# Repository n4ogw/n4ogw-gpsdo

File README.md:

# N4OGW GPS Disciplined oscillator

This GPSDO is based on the Lars Walenius design posted on eevblog.com:

[https://www.eevblog.com/forum/projects/lars-diy-gpsdo-with-arduino-and-1ns-resolution-tic/](https://www.eevblog.com/forum/projects/lars-diy-gpsdo-with-arduino-and-1ns-resolution-tic/)

The code has been translated from the Arduino to PIC, a
PIC18F27Q84. Unlike the original design external ICs are not used to
divide the 10 MHz input or measure the phase difference between the 1
PPS signal and the input. Instead, PIC Configurable Logic Cell (CLC)
units are used to perform these functions. The only active devices
besides the PIC are an op amp to buffer the PWM output controlling the
OCXO, and an op amp buffer and inverter gate to buffer the sine wave
OCXO output.

## Features

* Time interval Counter (TIC) with range of 1000 ns and 0.24 ns/bit
resolution (12 bit ADC)
* 16 bit PWM output for controlling the OCXO
* Direct frequency count of 10 MHz input to monitor frequency
* serial connections for computer and GPS
* LCD display showing UTC time, 6 character grid square, PWM value, lock status, number of satellites, and frequency counter error

---

## Description of hardware

The OCXO is a UCT 108663 with sine wave output. This OCXO requires a
12 V supply. The voltage on the EFC pin for mine is about 5 V when
tuned for 10 MHZ. RV2 is adjusted to first set the frequency of the
OCXO close to 10 MHz. The OCXO is buffered with an ADA4851 op amp and
sent to a 74LVC1G14 inverter before going to the PIC input. The PIC is
a PIC18F27Q84. A PIC18F26Q84 should also work.

 The PIC PWM output is buffered by two op amp stages using an
LM358. The PIC PWM output is set up as a single 16 bit PWM, but a
second pin is available for combining two PWM outputs.  A voltage
regulator on the board generates 5 V for the PIC and the GPS module.
Resistor R17 is not used. The value of R12/R13 depend on whether
current limiting is needed for the LCD backlight; mine did not need
it, so I used a zero ohm jumper. R23 is also a zero ohm jumper.

---

## Description of PIC code

MPLab 6.05; XC8 2.40

### Pins

RA0 - RA7 : (outputs) data for 2x16 LCD in 8 bit mode

RB0 : LCD RS (output)

RB1 : ADC input; reads TIC voltage

RB2 : (input) 10 MHz in

RB3 : (output) TIC to 3.9 k resistor

RB4 : button 1 (input)

RB5 : button 2 (input)

RB6 : ICSP clock

RB7 : ICSP data

RC0 : (input) PPS in

RC1 : LCD E (output)

RC2 : (input) UART2 RX (GPS)

RC3 : (output) UART2 TX (GPS)

RC4 : unused; can be used as second PWM output combined with RC5

RC5 : (output) 16 bit PWM output

RC6 : (output) UART1 TX (computer)

RC7 : (input) UART1 RX  (computer)

### Frequency counter

The PIC Signal Measurement Timer (SMT) is used as a frequency counter
to directly count the 10 MHz input signal. The SMT is used in Counter
mode; the signal comes from SMT1SIGPPS connected to RB2 (10 MHz); the
window comes from SMT1WINPPS connected to RC0 (PPS). Period is set to
0xFFFFFF, pulse width acquisition interrupt is enabled.

In this mode, the interrupt function `SMT1_PW_ACQ_ISR` is called at
every PPS pulse. This function updates the total count and the error
compared to 10 MHz.

### TIC

In the original design, an external IC is used to divide the 10 MHz
down to 1 MHz to drive the TIC. This function is instead done using
PIC CLC gates, one D-type flip-flop (CLC2) configured as divide-by-two
followed by three JK flip-flops (CLC3, CLC5, CLC6) configured as
divide-by-five.  CLCIN2 is connected to RB2, 10 MHz in. The output of
CLC6 is the 1.0 MHz signal.

####CLC2 (divide by 2)

####CLC3, CLC5, CLC6 (divide by 5)

####CLC3

####CLC5

####CLC6

####CLC1 and CLC7 (2 input D flip-flops with R)

Configured as the phase detector of the TIC. The inputs to CLC1 are
from CLC6 (1.0 MHz) and CLCIN3, which is mapped to RC0 (PPS). The
inputs to CLC7 are also PPS, and the output of CLC1. The output of
CLC7 drives the diode of the TIC circuit (RB3).

CLC1

CLC7

The reference voltage of the ADC is set to 1.024 V using the FVR
voltage reference. The ADC is set to trigger on the output of
CLC7. The ADC interrupt is enabled; `adcInterrupt()` is the interrupt
function which reads the value of the TIC. With a 12-bit ADC this is
in the range 0-4095.

### Buttons

The two input buttons are debounced using CLC8 and timer 6. CLCIN6 and
CLCIN7 are mapped to the two button pins, RB4 and RB5. Timer 6
is set up in monostable mode with a period of 15 ms, with the output
of CLC8 as the reset source. The timer interrupt function is
`buttonInterrupt()`, which checks to see which button was pressed.

####CLC8

####2x16 LCD

2x16 LCD library adopted from

[https://github.com/eziya/PIC18F_HD44780](https://github.com/eziya/PIC18F_HD44780)

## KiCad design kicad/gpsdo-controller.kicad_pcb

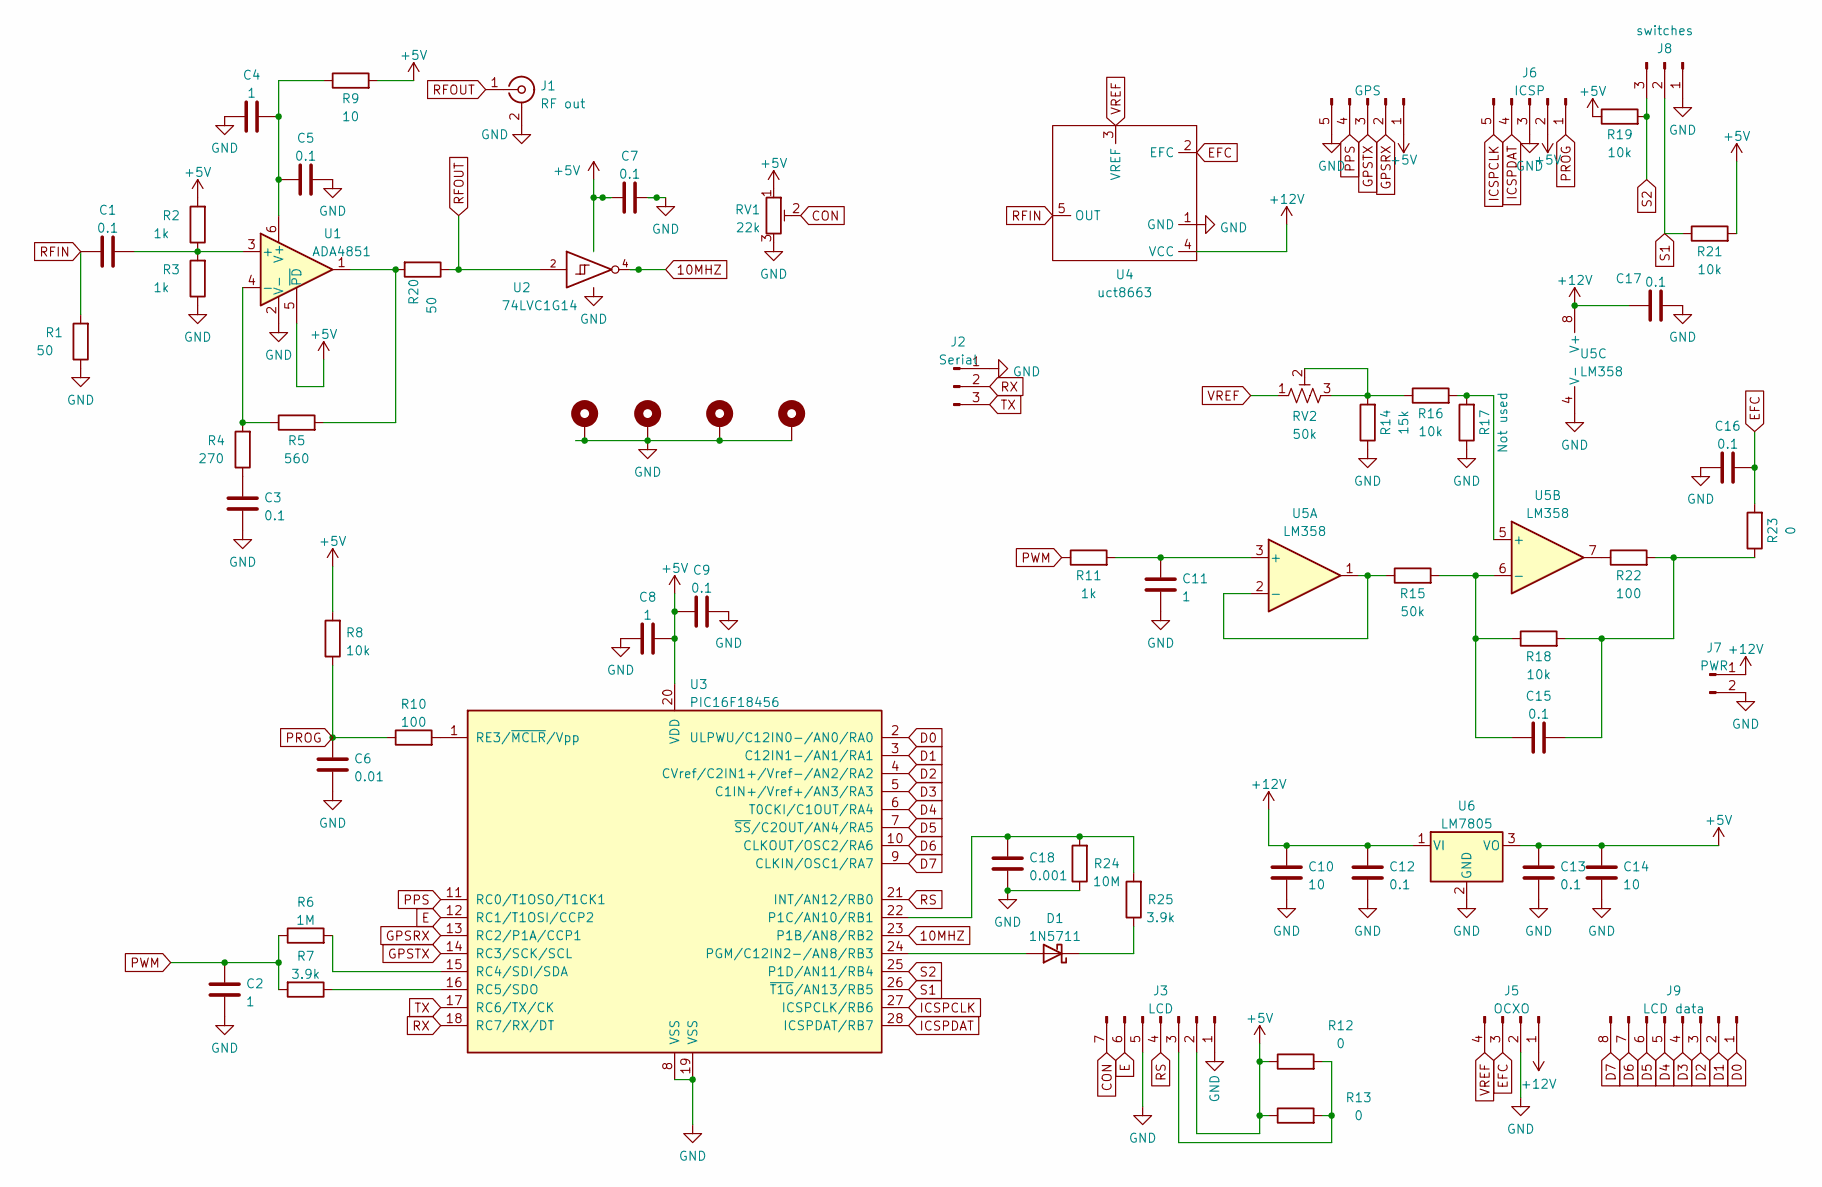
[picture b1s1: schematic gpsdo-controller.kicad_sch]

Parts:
C1, C3, C5, C7, C9, C12, C13, C15, C16, C17: 0.1; C_0805_2012Metric_Pad1.18x1.45mm_HandSolder
C2, C4, C8, C11: 1; C_0805_2012Metric_Pad1.18x1.45mm_HandSolder
C6: 0.01; C_0805_2012Metric_Pad1.18x1.45mm_HandSolder
C10, C14: 10; C_0805_2012Metric_Pad1.18x1.45mm_HandSolder
C18: 0.001; C_0805_2012Metric_Pad1.18x1.45mm_HandSolder
D1: 1N5711; D_SOD-123
H1, H2, H3, H4: GND; MountingHole_3.2mm_M3_DIN965_Pad
J1: RF out; SMA_Amphenol_901-144_Vertical
J2: Serial; PinHeader_1x03_P2.54mm_Vertical
J3: LCD; PinHeader_1x07_P2.54mm_Vertical
J4: GPS; PinHeader_1x05_P2.54mm_Vertical
J5: OCXO; PinHeader_1x04_P2.54mm_Vertical
J6: ICSP; PinHeader_1x05_P2.54mm_Vertical
J7: PWR; PinHeader_1x02_P2.54mm_Vertical
J8: switches; PinHeader_1x03_P2.54mm_Vertical
J9: LCD data; PinHeader_1x08_P2.54mm_Vertical
R1, R20: 50; R_0805_2012Metric_Pad1.20x1.40mm_HandSolder
R2, R3, R11: 1k; R_0805_2012Metric_Pad1.20x1.40mm_HandSolder
R4: 270; R_0805_2012Metric_Pad1.20x1.40mm_HandSolder
R5: 560; R_0805_2012Metric_Pad1.20x1.40mm_HandSolder
R6: 1M; R_0805_2012Metric_Pad1.20x1.40mm_HandSolder
R7, R25: 3.9k; R_0805_2012Metric_Pad1.20x1.40mm_HandSolder
R8, R16, R18, R19, R21: 10k; R_0805_2012Metric_Pad1.20x1.40mm_HandSolder
R9: 10; R_0805_2012Metric_Pad1.20x1.40mm_HandSolder
R10, R22: 100; R_0805_2012Metric_Pad1.20x1.40mm_HandSolder
R12: 0; R_1210_3225Metric_Pad1.30x2.65mm_HandSolder
R13, R23: 0; R_0805_2012Metric_Pad1.20x1.40mm_HandSolder
R14: 15k; R_0805_2012Metric_Pad1.20x1.40mm_HandSolder
R15: 50k; R_0805_2012Metric_Pad1.20x1.40mm_HandSolder
R17: Not used; R_0805_2012Metric_Pad1.20x1.40mm_HandSolder
R24: 10M; R_0805_2012Metric_Pad1.20x1.40mm_HandSolder
RV1: 22k; Potentiometer_Vishay_T7-YA_Single_Vertical
RV2: 50k; Potentiometer_Bourns_3299Y_Vertical
U1: ADA4851; SOT-23-6
U2: 74LVC1G14; SOT-353_SC-70-5_Handsoldering
U3: PIC16F18456; DIP-28_W7.62mm
U4: uct8663
U5: LM358; DIP-8_W7.62mm
U6: LM7805; TO-220-3_Vertical

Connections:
10MHZ: U2.4, U3.23 (P1B/AN8/RB2)
+5V: C7.1, C8.2, C9.1, C13.2, C14.2, J3.2, J4.1, J6.2, R2.2, R8.2, R9.2, R12.1, R13.1, R19.1, R21.2, RV1.1, U1.5 (~PD), U2.5 (VCC), U3.20 (VDD), U6.3 (VO)
+12V: C10.2, C12.2, C17.1, J5.1, J7.1, U4.4 (VCC), U5.8 (V+), U6.1 (VI)
CON: J3.7, RV1.2
D0: J9.1, U3.2 (ULPWU/C12IN0-/AN0/RA0)
D1: J9.2, U3.3 (C12IN1-/AN1/RA1)
D2: J9.3, U3.4 (CVref/C2IN1+/Vref-/AN2/RA2)
D3: J9.4, U3.5 (C1IN+/Vref+/AN3/RA3)
D4: J9.5, U3.6 (T0CKI/C1OUT/RA4)
D5: J9.6, U3.7 (~SS/C2OUT/AN4/RA5)
D6: J9.7, U3.10 (CLKOUT/OSC2/RA6)
D7: J9.8, U3.9 (CLKIN/OSC1/RA7)
E: J3.6, U3.12 (RC1/T1OSI/CCP2)
EFC: C16.1, J5.3, R23.2, U4.2 (EFC)
GND: C2.1, C3.1, C4.1, C5.2, C6.1, C7.2, C8.1, C9.2, C10.1, C11.1, C12.1, C13.1, C14.1, C16.2, C17.2, C18.1, H1.1, H2.1, H3.1, H4.1, J1.2 (Ext), J2.1, J3.1, J3.5, J4.5, J5.2, J6.3, J7.2, J8.1, R1.1, R3.1, R14.1, R17.1, R24.1, RV1.3, U1.2 (V-), U2.3 (GND), U3.8 (VSS), U3.19 (VSS), U4.1 (GND), U5.4 (V-), U6.2 (GND)
GPSRX: J4.2, U3.13 (RC2/P1A/CCP1)
GPSTX: J4.3, U3.14 (RC3/SCK/SCL)
ICSPCLK: J6.5, U3.27 (ICSPCLK/RB6)
ICSPDAT: J6.4, U3.28 (ICSPDAT/RB7)
unnamed: C1.2, R2.1, R3.2, U1.3 (+)
unnamed: C3.2, R4.1
unnamed: C4.2, C5.1, R9.1, U1.6 (V+)
unnamed: C11.2, R11.2, U5.3 (+)
unnamed: C15.1, R15.2, R18.1, U5.6 (-)
unnamed: C15.2, R18.2, R22.2, R23.1
unnamed: C18.2, R24.2, R25.2, U3.22 (P1C/AN10/RB1)
unnamed: D1.1 (K), R25.1
unnamed: D1.2 (A), U3.24 (PGM/C12IN2-/AN8/RB3)
unnamed: J3.3, R12.2, R13.2
unnamed: R4.2, R5.1, U1.4 (-)
unnamed: R6.2, U3.15 (RC4/SDI/SDA)
unnamed: R7.1, U3.16 (RC5/SDO)
unnamed: R10.2, U3.1 (RE3/~MCLR/Vpp)
unnamed: R14.2, R16.1, RV2.2, RV2.3
unnamed: R15.1, U5.1, U5.2 (-)
unnamed: R16.2, R17.2, U5.5 (+)
unnamed: R5.2, R20.2, U1.1
unnamed: R22.1, U5.7
PPS: J4.4, U3.11 (RC0/T1OSO/T1CK1)
PROG: C6.2, J6.1, R8.1, R10.1
PWM: C2.2, R6.1, R7.2, R11.1
RFIN: C1.1, R1.2, U4.5 (OUT)
RFOUT: J1.1 (In), R20.1, U2.2
RS: J3.4, U3.21 (INT/AN12/RB0)
RX: J2.2, U3.18 (RC7/RX/DT)
S1: J8.2, R21.1, U3.26 (~T1G/AN13/RB5)
S2: J8.3, R19.2, U3.25 (P1D/AN11/RB4)
TX: J2.3, U3.17 (RC6/TX/CK)
VREF: J5.4, RV2.1, U4.3 (VREF)

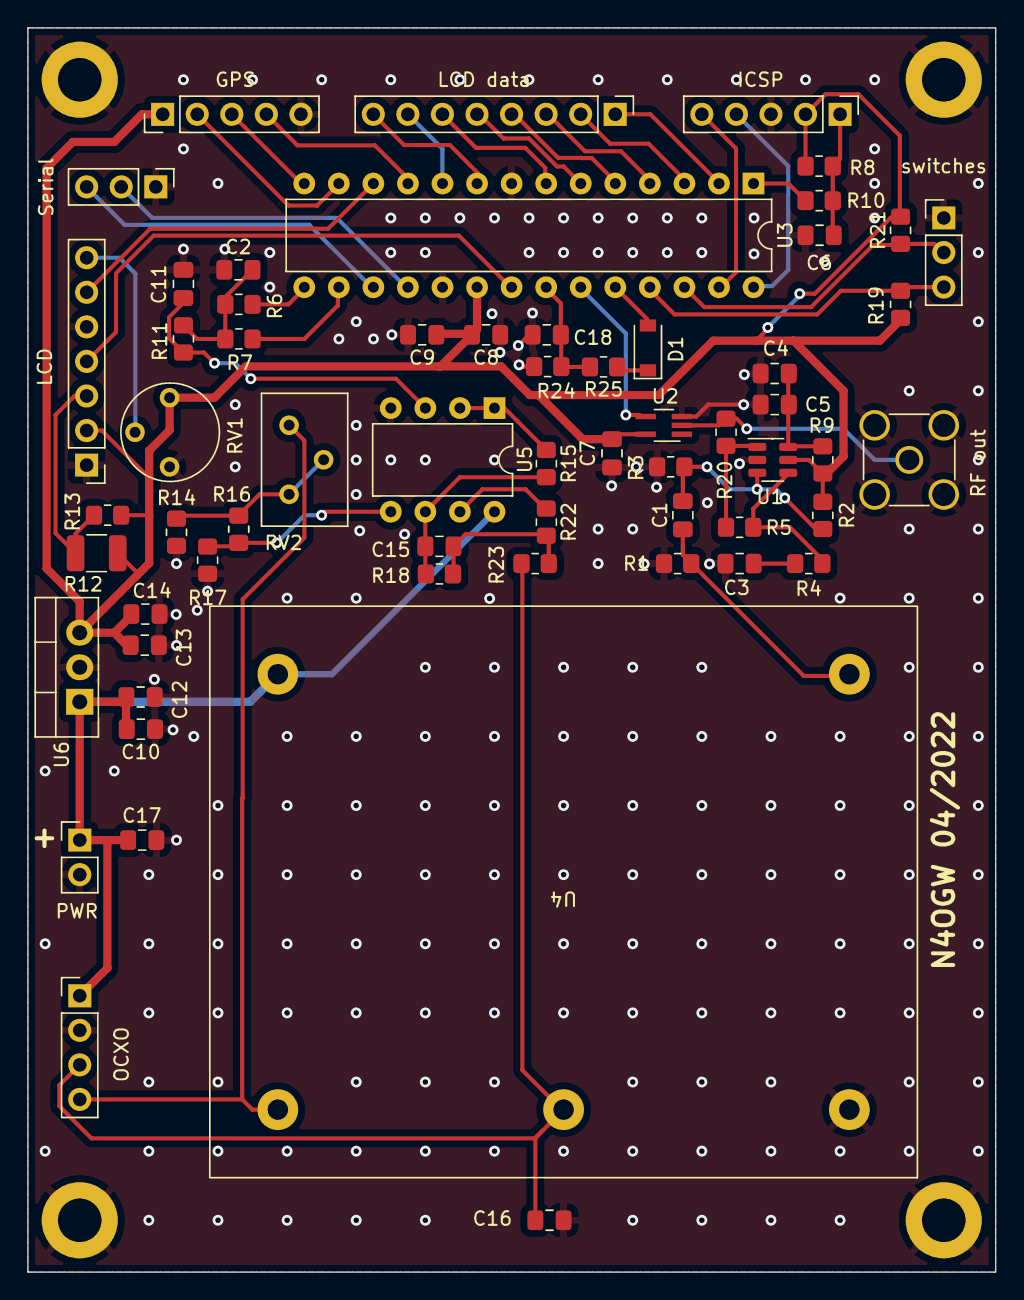
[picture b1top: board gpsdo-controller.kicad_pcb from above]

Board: 2 copper layers, 71.1 x 91.4 mm, 65 parts (0 on the bottom side), 49 nets.

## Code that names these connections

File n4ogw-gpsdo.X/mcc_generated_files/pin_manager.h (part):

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#define RA0_SetHigh()            do { LATAbits.LATA0 = 1; } while(0)
#define RA0_SetLow()             do { LATAbits.LATA0 = 0; } while(0)
#define RA0_Toggle()             do { LATAbits.LATA0 = ~LATAbits.LATA0; } while(0)
#define RA0_GetValue()              PORTAbits.RA0
#define RA0_SetDigitalInput()    do { TRISAbits.TRISA0 = 1; } while(0)
#define RA0_SetDigitalOutput()   do { TRISAbits.TRISA0 = 0; } while(0)
#define RA0_SetPullup()             do { WPUAbits.WPUA0 = 1; } while(0)
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// get/set channel_ANB1 aliases
#define channel_ANB1_TRIS                 TRISBbits.TRISB1
#define channel_ANB1_LAT                  LATBbits.LATB1
#define channel_ANB1_PORT                 PORTBbits.RB1
#define channel_ANB1_WPU                  WPUBbits.WPUB1
#define channel_ANB1_OD                   ODCONBbits.ODCB1
#define channel_ANB1_ANS                  ANSELBbits.ANSELB1
#define channel_ANB1_SetHigh()            do { LATBbits.LATB1 = 1; } while(0)
#define channel_ANB1_SetLow()             do { LATBbits.LATB1 = 0; } while(0)
#define channel_ANB1_Toggle()             do { LATBbits.LATB1 = ~LATBbits.LATB1; } while(0)
#define channel_ANB1_GetValue()           PORTBbits.RB1
#define channel_ANB1_SetDigitalInput()    do { TRISBbits.TRISB1 = 1; } while(0)
#define channel_ANB1_SetDigitalOutput()   do { TRISBbits.TRISB1 = 0; } while(0)
#define channel_ANB1_SetPullup()          do { WPUBbits.WPUB1 = 1; } while(0)
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#define RB2_SetHigh()            do { LATBbits.LATB2 = 1; } while(0)
#define RB2_SetLow()             do { LATBbits.LATB2 = 0; } while(0)
#define RB2_Toggle()             do { LATBbits.LATB2 = ~LATBbits.LATB2; } while(0)
#define RB2_GetValue()              PORTBbits.RB2
#define RB2_SetDigitalInput()    do { TRISBbits.TRISB2 = 1; } while(0)
#define RB2_SetDigitalOutput()   do { TRISBbits.TRISB2 = 0; } while(0)
#define RB2_SetPullup()             do { WPUBbits.WPUB2 = 1; } while(0)
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#define RB3_SetHigh()            do { LATBbits.LATB3 = 1; } while(0)
#define RB3_SetLow()             do { LATBbits.LATB3 = 0; } while(0)
#define RB3_Toggle()             do { LATBbits.LATB3 = ~LATBbits.LATB3; } while(0)
#define RB3_GetValue()              PORTBbits.RB3
#define RB3_SetDigitalInput()    do { TRISBbits.TRISB3 = 1; } while(0)
#define RB3_SetDigitalOutput()   do { TRISBbits.TRISB3 = 0; } while(0)
#define RB3_SetPullup()             do { WPUBbits.WPUB3 = 1; } while(0)
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#define RB4_SetHigh()            do { LATBbits.LATB4 = 1; } while(0)
#define RB4_SetLow()             do { LATBbits.LATB4 = 0; } while(0)
#define RB4_Toggle()             do { LATBbits.LATB4 = ~LATBbits.LATB4; } while(0)
#define RB4_GetValue()              PORTBbits.RB4
#define RB4_SetDigitalInput()    do { TRISBbits.TRISB4 = 1; } while(0)
#define RB4_SetDigitalOutput()   do { TRISBbits.TRISB4 = 0; } while(0)
#define RB4_SetPullup()             do { WPUBbits.WPUB4 = 1; } while(0)
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#define RB5_SetHigh()            do { LATBbits.LATB5 = 1; } while(0)
#define RB5_SetLow()             do { LATBbits.LATB5 = 0; } while(0)
#define RB5_Toggle()             do { LATBbits.LATB5 = ~LATBbits.LATB5; } while(0)
#define RB5_GetValue()              PORTBbits.RB5
#define RB5_SetDigitalInput()    do { TRISBbits.TRISB5 = 1; } while(0)
#define RB5_SetDigitalOutput()   do { TRISBbits.TRISB5 = 0; } while(0)
#define RB5_SetPullup()             do { WPUBbits.WPUB5 = 1; } while(0)
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#define RC0_SetHigh()            do { LATCbits.LATC0 = 1; } while(0)
#define RC0_SetLow()             do { LATCbits.LATC0 = 0; } while(0)
#define RC0_Toggle()             do { LATCbits.LATC0 = ~LATCbits.LATC0; } while(0)
#define RC0_GetValue()              PORTCbits.RC0
#define RC0_SetDigitalInput()    do { TRISCbits.TRISC0 = 1; } while(0)
#define RC0_SetDigitalOutput()   do { TRISCbits.TRISC0 = 0; } while(0)
#define RC0_SetPullup()             do { WPUCbits.WPUC0 = 1; } while(0)
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#define RC2_SetHigh()            do { LATCbits.LATC2 = 1; } while(0)
#define RC2_SetLow()             do { LATCbits.LATC2 = 0; } while(0)
#define RC2_Toggle()             do { LATCbits.LATC2 = ~LATCbits.LATC2; } while(0)
#define RC2_GetValue()              PORTCbits.RC2
#define RC2_SetDigitalInput()    do { TRISCbits.TRISC2 = 1; } while(0)
#define RC2_SetDigitalOutput()   do { TRISCbits.TRISC2 = 0; } while(0)
#define RC2_SetPullup()             do { WPUCbits.WPUC2 = 1; } while(0)
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#define RC3_SetHigh()            do { LATCbits.LATC3 = 1; } while(0)
#define RC3_SetLow()             do { LATCbits.LATC3 = 0; } while(0)
#define RC3_Toggle()             do { LATCbits.LATC3 = ~LATCbits.LATC3; } while(0)
#define RC3_GetValue()              PORTCbits.RC3
#define RC3_SetDigitalInput()    do { TRISCbits.TRISC3 = 1; } while(0)
#define RC3_SetDigitalOutput()   do { TRISCbits.TRISC3 = 0; } while(0)
#define RC3_SetPullup()             do { WPUCbits.WPUC3 = 1; } while(0)
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#define RC5_SetHigh()            do { LATCbits.LATC5 = 1; } while(0)
#define RC5_SetLow()             do { LATCbits.LATC5 = 0; } while(0)
#define RC5_Toggle()             do { LATCbits.LATC5 = ~LATCbits.LATC5; } while(0)
#define RC5_GetValue()              PORTCbits.RC5
#define RC5_SetDigitalInput()    do { TRISCbits.TRISC5 = 1; } while(0)
#define RC5_SetDigitalOutput()   do { TRISCbits.TRISC5 = 0; } while(0)
#define RC5_SetPullup()             do { WPUCbits.WPUC5 = 1; } while(0)
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#define RC6_SetHigh()            do { LATCbits.LATC6 = 1; } while(0)
#define RC6_SetLow()             do { LATCbits.LATC6 = 0; } while(0)
#define RC6_Toggle()             do { LATCbits.LATC6 = ~LATCbits.LATC6; } while(0)
#define RC6_GetValue()              PORTCbits.RC6
#define RC6_SetDigitalInput()    do { TRISCbits.TRISC6 = 1; } while(0)
#define RC6_SetDigitalOutput()   do { TRISCbits.TRISC6 = 0; } while(0)
#define RC6_SetPullup()             do { WPUCbits.WPUC6 = 1; } while(0)
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#define RC7_SetHigh()            do { LATCbits.LATC7 = 1; } while(0)
#define RC7_SetLow()             do { LATCbits.LATC7 = 0; } while(0)
#define RC7_Toggle()             do { LATCbits.LATC7 = ~LATCbits.LATC7; } while(0)
#define RC7_GetValue()              PORTCbits.RC7
#define RC7_SetDigitalInput()    do { TRISCbits.TRISC7 = 1; } while(0)
#define RC7_SetDigitalOutput()   do { TRISCbits.TRISC7 = 0; } while(0)
#define RC7_SetPullup()             do { WPUCbits.WPUC7 = 1; } while(0)
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
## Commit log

2023-02-17 add kicad
2023-02-17 fix typo
2023-02-17 add schematic
2023-02-19 add delay
2023-02-26 fix communication with Venus gps
2023-03-12 various code cleanups fix 3 hour storage of status
2023-04-05 Fix commands to set gps to 115200 baud
2023-04-28 Add error (checksum) checking of gps messages
2024-10-13 improve error checking of gps serial data

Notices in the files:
n4ogw-gpsdo.X/mcc_generated_files/pin_manager.h:
(c) 2018 Microchip Technology Inc. and its subsidiaries.
